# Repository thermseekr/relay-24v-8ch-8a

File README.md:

# eumesmo-rl-8ch8a

Relay board with 8x 24 VDC NO relays. This board is designed to be used togheter with [eumesmo-io-24v16ch](https://github.com/thermseekr/eumesmo-io-24v16ch), but can be driven by any 24V control circuit compatible with NPN inputs. It uses Omron 10A relays and is limited to 8A/channel per copper trace capacity.

The board is compatible with the SP7 DIN rail system from Metaltex.

## VERSION HISTORY

V1.2 - 2026/06/13 - Repository renamed from RELAY-24V-4CH-8A to eumesmo-rl-4ch8A to align the design with the eumesmo line of building automation products.

V1.1 - 2026/06/13 - Input terminal blocks replaced from 2.54mm to 3.5mm pitch for easier installation in the field.

V1.0 - 2024/11/24 - Initial release.

## LICENSE

This project is licensed under the [Creative Commons BY-NC 4.0 License](https://creativecommons.org/licenses/by-nc/4.0/).
Commercial use is not permitted without prior written consent. See the [LICENSE.txt](LICENSE.txt) file for details.

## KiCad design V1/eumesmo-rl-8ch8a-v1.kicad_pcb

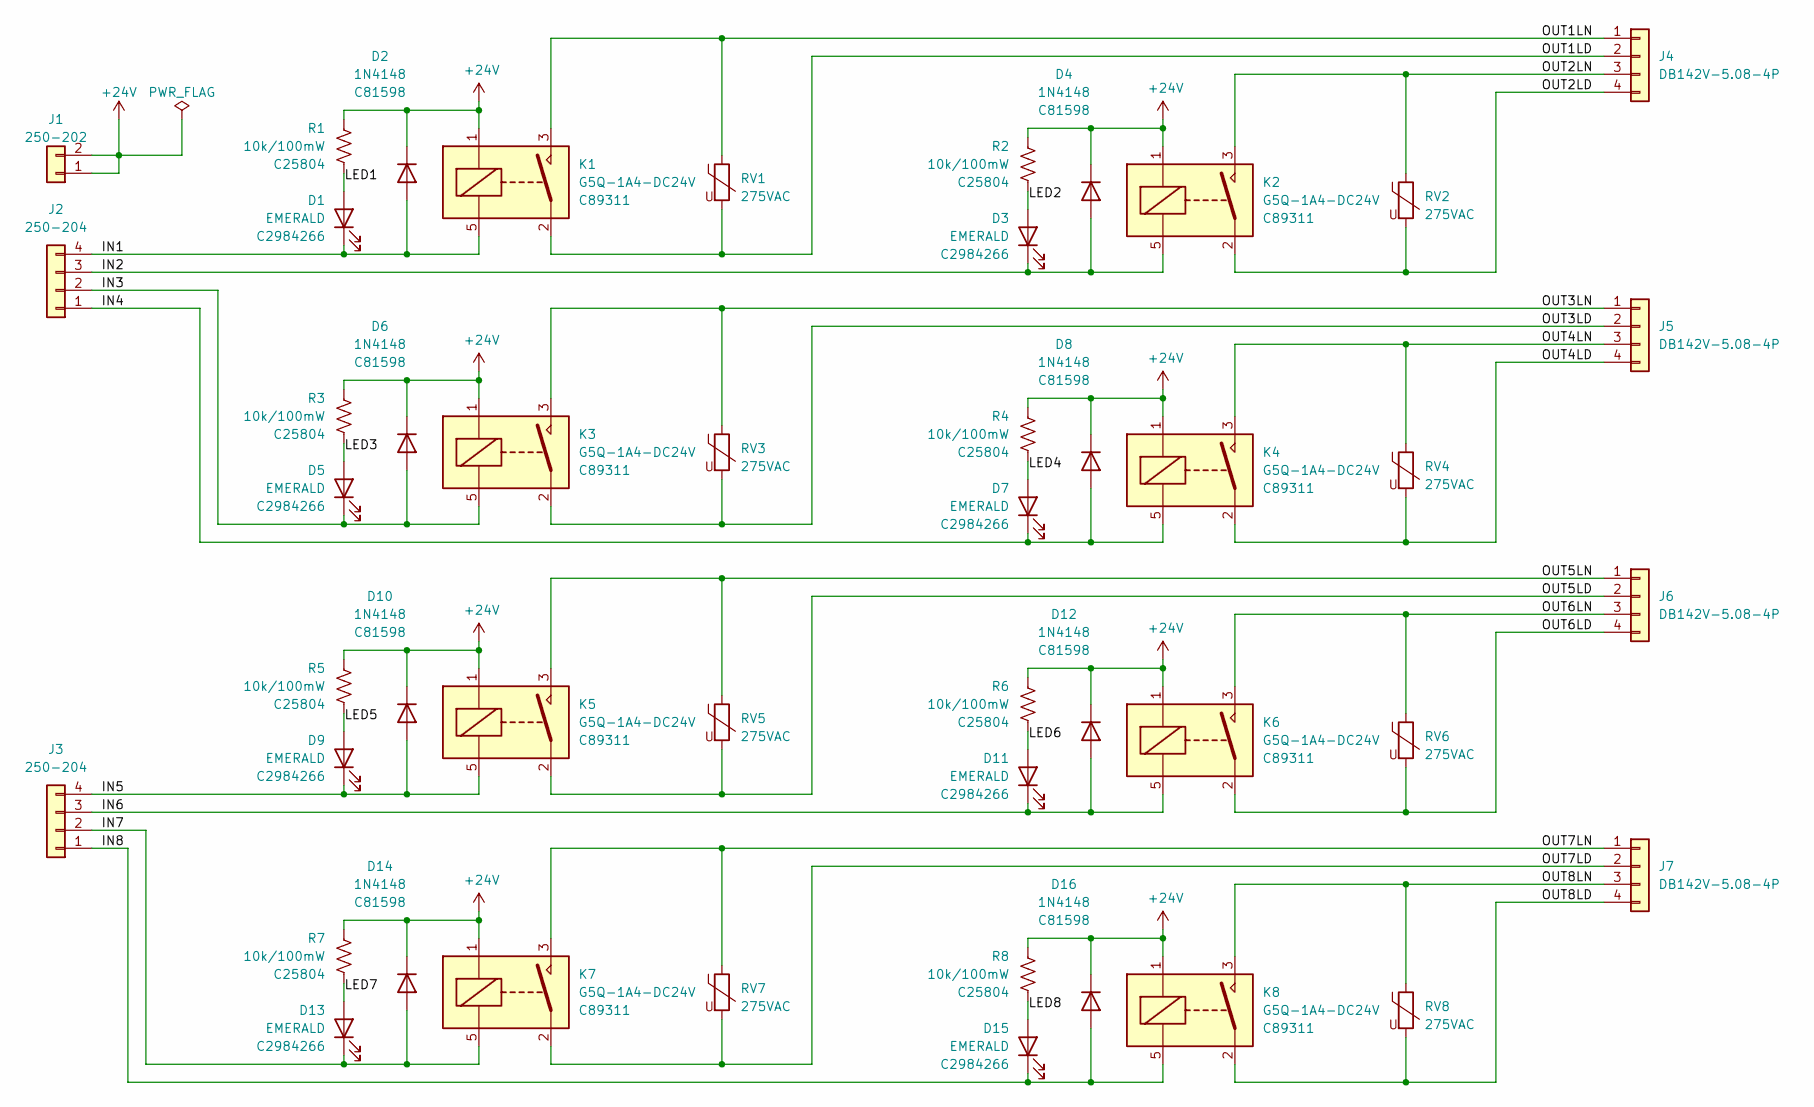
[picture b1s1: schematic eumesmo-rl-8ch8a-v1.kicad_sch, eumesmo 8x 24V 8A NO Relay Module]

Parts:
D1, D3, D5, D7, D9, D11, D13, D15: EMERALD; LED_0603_1608Metric; Mfr PN 19-213/GHC-XS1T1N/5T; LCSC Part # C2984266
D2, D4, D6, D8, D10, D12, D14, D16: 1N4148; D_SOD-123; Mfr PN 1N4148W; LCSC Part # C81598
J1: 250-202; TerminalBlock_Wago_250-202_1x02_P3.5mm_45Degree; Mfr PN 250-202; JLCPCB BOM 1
J2, J3: 250-204; TerminalBlock_Wago_250-204_1x04_P3.5mm_45Degree; Mfr PN 250-204; JLCPCB BOM 1
J4, J5, J6, J7: DB142V-5.08-4P; TerminalBlock_Dibo_DB142V-5.08-4P_1x04_P5.08mm_Vertical; Mfr PN DB142V-5.08-4P-GN; JLCPCB BOM 1
K1, K2, K3, K4, K5, K6, K7, K8: G5Q-1A4-DC24V; Relay_SPST_Omron-G5Q-1A; Mfr PN G5Q-1A4-DC24V; JLCPCB BOM 1
R1, R2, R3, R4, R5, R6, R7, R8: 10k/100mW; R_0603_1608Metric; Mfr PN 0603WAF1002T5E; LCSC Part # C25804
RV1, RV2, RV3, RV4, RV5, RV6, RV7, RV8: 275VAC; RV_Disc_D9.50mm_W3.6mm_P5.08mm; Mfr PN RM07D431KC1IE100; JLCPCB BOM 1

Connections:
+24V: D2.1 (K), D4.1 (K), D6.1 (K), D8.1 (K), D10.1 (K), D12.1 (K), D14.1 (K), D16.1 (K), J1.1, J1.2, K1.1, K2.1, K3.1, K4.1, K5.1, K6.1, K7.1, K8.1, R1.1, R2.1, R3.1, R4.1, R5.1, R6.1, R7.1, R8.1
/IN1: D1.1 (K), D2.2 (A), J2.4, K1.5
/IN2: D3.1 (K), D4.2 (A), J2.3, K2.5
/IN3: D5.1 (K), D6.2 (A), J2.2, K3.5
/IN4: D7.1 (K), D8.2 (A), J2.1, K4.5
/IN5: D9.1 (K), D10.2 (A), J3.4, K5.5
/IN6: D11.1 (K), D12.2 (A), J3.3, K6.5
/IN7: D13.1 (K), D14.2 (A), J3.2, K7.5
/IN8: D15.1 (K), D16.2 (A), J3.1, K8.5
/LED1: D1.2 (A), R1.2
/LED2: D3.2 (A), R2.2
/LED3: D5.2 (A), R3.2
/LED4: D7.2 (A), R4.2
/LED5: D9.2 (A), R5.2
/LED6: D11.2 (A), R6.2
/LED7: D13.2 (A), R7.2
/LED8: D15.2 (A), R8.2
/OUT1LD: J4.2, K1.2, RV1.2
/OUT1LN: J4.1, K1.3, RV1.1
/OUT2LD: J4.4, K2.2, RV2.2
/OUT2LN: J4.3, K2.3, RV2.1
/OUT3LD: J5.2, K3.2, RV3.2
/OUT3LN: J5.1, K3.3, RV3.1
/OUT4LD: J5.4, K4.2, RV4.2
/OUT4LN: J5.3, K4.3, RV4.1
/OUT5LD: J6.2, K5.2, RV5.2
/OUT5LN: J6.1, K5.3, RV5.1
/OUT6LD: J6.4, K6.2, RV6.2
/OUT6LN: J6.3, K6.3, RV6.1
/OUT7LD: J7.2, K7.2, RV7.2
/OUT7LN: J7.1, K7.3, RV7.1
/OUT8LD: J7.4, K8.2, RV8.2
/OUT8LN: J7.3, K8.3, RV8.1

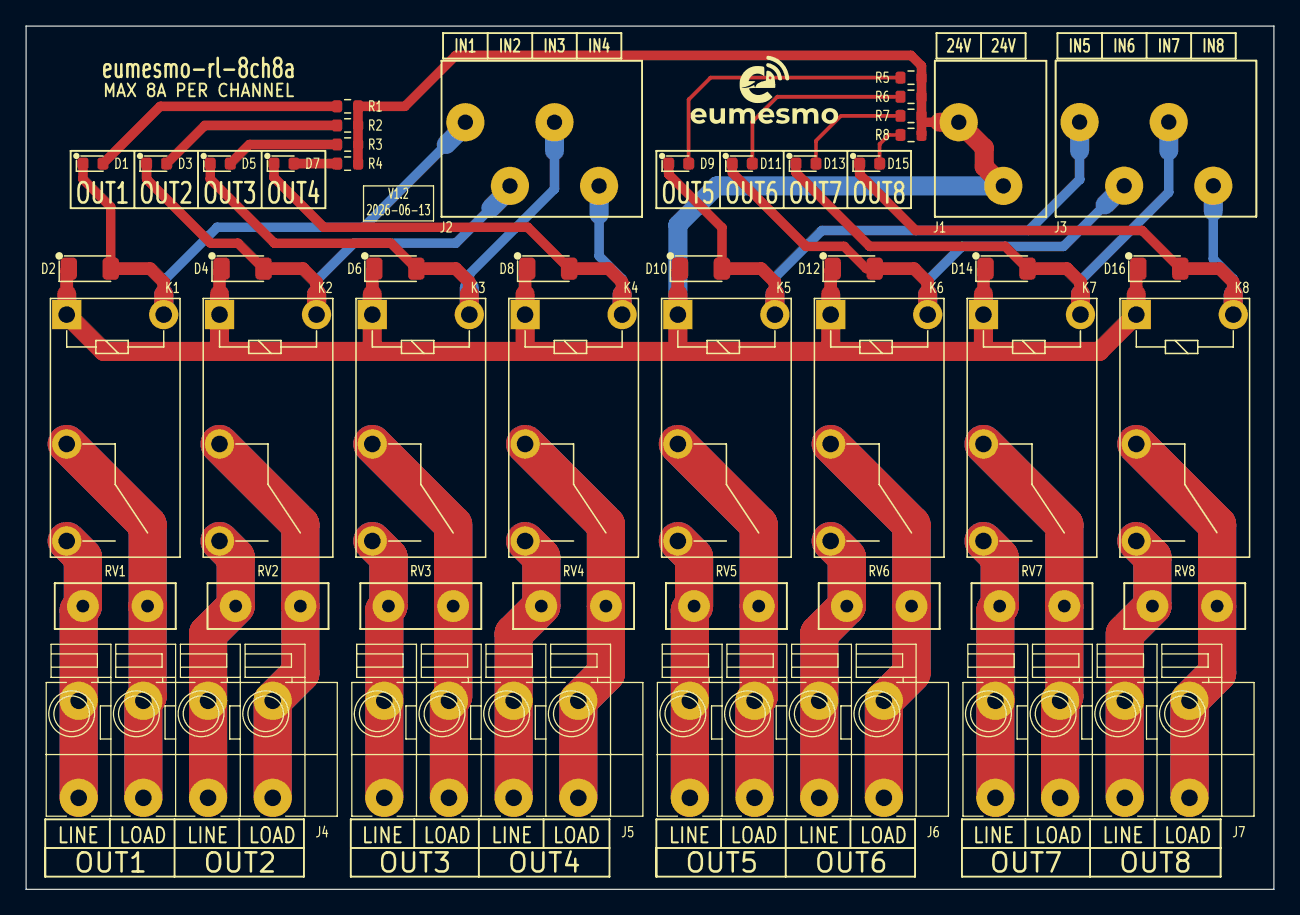
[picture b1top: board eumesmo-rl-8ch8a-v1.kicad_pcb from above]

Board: 2 copper layers, 98.0 x 67.8 mm, 47 parts (0 on the bottom side), 33 nets.

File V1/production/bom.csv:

Designator,Footprint,Quantity,Value,LCSC Part #
"D1, D11, D13, D15, D3, D5, D7, D9",0603,8,EMERALD,C2984266
"D10, D12, D14, D16, D2, D4, D6, D8",D_SOD-123,8,1N4148,C81598
J1,TerminalBlock_Wago_250-202_1x02_P3.5mm_45Degree,1,250-202,C2765061
"J2, J3",TerminalBlock_Wago_250-204_1x04_P3.5mm_45Degree,2,250-204,C2765063
"J4, J5, J6, J7",TerminalBlock_Dibo_DB142V-5.08-4P_1x04_P5.08mm_Vertical,4,DB142V-5.08-4P,C2898701
"K1, K2, K3, K4, K5, K6, K7, K8",Relay_SPST_Omron-G5Q-1A,8,G5Q-1A4-DC24V,C89311
"R1, R2, R3, R4, R5, R6, R7, R8",0603,8,10k/100mW,C25804
"RV1, RV2, RV3, RV4, RV5, RV6, RV7, RV8",RV_Disc_D9.50mm_W3.6mm_P5.08mm,8,275VAC,C2761646

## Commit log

2025-04-14 Prefab checks
2025-04-16 Updated footprints
2025-06-22 Updated connectors
2025-06-30 Added license
2025-12-13 Review before fabrication
2025-12-19 Revising before manufacturing.
2026-06-12 Replaced input terminal blocks for 3.5mm pitch.
2026-06-13 Small adjustments to silkscreen
2026-06-13 Renamed files to align with eumesmo branding.
